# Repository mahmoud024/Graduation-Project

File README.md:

<h1 align="center">Graduation Project</h1>

## Our Idea

The goal of this project is to construct a physical FANET, outside the simulator, this can be done by constructing a number of drones built on the ESP-Drone repository, along with our own PCB and a 3D printed drone body. The FANET nodes will communicate with each other using LoRaWAN through our own modified AODV routing protocol. The FANET is planned to operate over the area of Birzeit University.

Since we will be using light-weight drones for nodes, the weight of anything carried by drones is critical, for this reason we decided on using the LoRa32 microcontroller, that integrates the ESP32 chip along with the LoRa module in a compact package, which weighs about 18grams, our testing shows a current draw of 45-50 mA during normal operations, goes up by 10 mA during transmission/reception

<div align="center">
  
</div>

## Step 1: Build ESP23 Drone

Since the scope of the project is rapidly expanding, we don’t have enough time
to design and build a drone from scratch, instead we will be using Espressif
Systems’ drone design.

For more information on getting started, visit the [Espressif ESP-Drone Documentation](https://docs.espressif.com/projects/espressif-esp-drone/en/latest/getespidf.html).

<h3 align="center">Hardware Part</h3>
   
1. **Components**

    We faced some difficulties in providing the parts because we are restricted by the Israeli occupation and the high cost of the parts, but the parts were eventually provided with great difficulty.

    - ##### Basic Component List
    <div align="center">
      
      | **Component**                         | **Number** | **Notes**                         |
      |---------------------------------------|------------|-----------------------------------|
      | Main board                            | 1          | ESP32 LORA V3 + MPU6050           |
      | Frame                                 | 1          | We Build it using 3D printer      |
      | 716 motor                             | 4          | Optional: 720 motor               |
      | 46mm propeller A                      | 2          |                                   |
      | 46mm propeller B                      | 2          |                                   |
      | 1000mAh 1s LiPo battery               | 1          |                                   |
      
    </div>

     1. **Frame**

      Steps to make the Frame:

      <div align="center">
          
      </div>

   Final Output:
   
    <div align="center">

    </div>

     2. **Main Controller**

      <div align="center">
          
      </div>

    <div align="center">

      | **Chip**       | **Module**           |     **Battery**       |    **Dimensions**     |
      |----------------|----------------------|-----------------------|-----------------------|
      | ESP32-S3FN8    | ESP32 LORA V3        | 3.7V lithium battery  |  50.2 * 25.5* 10.2 mm |

    </div>

     3. **Sensor**
        
      <div align="center">
          
      </div>
   
    <div align="center">
  
      | **Sensor**     | **Interface**        | **Notes**                             |
      |----------------|----------------------|---------------------------------------|
      | MPU6050        | I2C0                 | Main board sensor                     |
   
    </div>

    3. **Motor**
        
      <div align="center">
          
      </div>
   
    <div align="center">
  
      | **Motor**      | **Type**             | **Notes**                              |
      |----------------|----------------------|----------------------------------------|
      | 716 motor      | Coreless motor       | Use 720 if you have issue in altitude  |
   
    </div>

    3. **Battery**
        
      <div align="center">
          
      </div>
   
    <div align="center">
  
      | **Battery**             | **Voltage**     | **Dimensions**      | **Dimensions**    |
      |-------------------------|-----------------|---------------------|-------------------|
      | 1000mAh 1s LiPo battery | 3.7V (1S)       | 48 x 30 x 9         | 28.5              |
   
    </div>

    - ##### Definition of Main Board IO

    <div align="center">

      | **Pins**       | **Function**         | **Notes**                             |
      |----------------|----------------------|---------------------------------------|
      | GPIO23         | I2C0_SDA             | Only for MPU6050                      |
      | GPIO22         | I2C0_SCL             | Only for MPU6050                      |
      | GPIO2          | interrupt            | MPU6050 interrupt                     |
      | GPIO12         | MOT_1                |                                       |
      | GPIO35         | MOT_2                |                                       |
      | GPIO32         | MOT_3                |                                       |
      | GPIO33         | MOT_4                |                                       |
      | GND            |                      | With Ground                           |
      | 3V3            |                      | With VCC of MPU6050                   |

    </div>

2. **PCB**

    As is previously, our drone design is light-weight, so we will need to conserve as much as possible on the drone weight, and therefore we found it best to construct our own PCB.

    Scheme Below show our PCB design:

    <div align="center">
      
    </div>

    Steps to make our PCB:

    <div align="center">

    </div>

    The Link below show some videos While working on the production of the PCB (https://google.com)

    You Can Find All File You Needed in (PCB) Folder
---

<h3 align="center">Software Part</h3>

#### Set up ESP-IDF Environment

Please refer to [ ESP-IDF Programming Guide](https://docs.espressif.com/projects/esp-idf/en/release-v4.4/esp32s2/get-started/index.html) and set up ESP-IDF environmnet step by step.

* ESP-IDF branch release /v4.4 is suggested.

* Please follow and complete all setup steps.

* Build a example of ESP-IDF to make sure the setup is successful.

#### Get Project Source Code
###### Beta code, currently in the GitHub repository, is available by using git:

```
git clone https://github.com/espressif/esp-drone.git
```
###### The project software mainly consists of a flight control kernel, hardware drivers, and dependency libraries:

* The flight control kernel is from Crazyflie, mainly including hardware abstraction layer and flight control program.

* Hardware drivers are structured in files according to hardware interfaces, including I2C devcies and SPI devices.

* Dependency libraries include the default components provided by ESP-IDF, as well as DSP from third parties.

###### The code file structure is as follows:

#### Download and Install ESP-Drone APP

ESP-Drone APP is available for Android and iOS.

For Android, please scan the QR below to download ESP-Drone APP.

<div align="center">
  
</div>

For iOS, please search and download the ESP-Drone APP in App Store.

iOS APP source code: [ESP-Drone-iOS](https://github.com/EspressifApps/ESP-Drone-iOS)

Android APP source code: [ESP-Drone-Android](https://github.com/EspressifApps/ESP-Drone-Android)

#### Flight Control

* Click “Connect” button/icon at your APP. When the connection is established successfully between your drone and APP, the LED on the drone blinks GREEN.

* Slide “Thrust” slightly to take off the drone.

* Control the flight by moving your fingers on the APP.

<div align="center">
  
</div>

<div align="center">
  Android APP Interface
</div>

## Step 2: Routing Protocol

we will be using a LoRa module for transmission/Re- ception between nodes in our physical test bench, the LoRa module is chosen for its extended range, up to 14Km at SF12, and extremely low current draw, our own testing showed an 10 mA increase in current draw at transmission/re- ception at SF7, matching the datasheet specification.

The drawback to all this, is the low bandwidth, 290 bps at SF12, choosing a lower spread factor, will provide a higher bandwidth at a lower range, SF7 is rated to give 5470 bps for 2km, a range of 2km is well above our needs for this project, the bit rate is also sufficient for the communication protocol used, table 2 shows LoRa transmission ranges and bandwidth at different Spread Factors.

<div align="center">
  
  | **Spreading Factor** | **Bitrate** | **Range** |
  |----------------------|-------------|-----------|
  | SF7                  | 5470 bps    | 2 Km      |
  | SF8                  | 3125 bps    | 4 Km      |
  | SF9                  | 1760 bps    | 6 Km      |
  | SF10                 | 980 bps     | 8 Km      |
  | SF11                 | 440 bps     | 11 Km     |
  | SF12                 | 290 bps     | 14 Km     |

</div>

Our routing protocol builds upon the AODV protocol, and improves on it in two substantial ways, multiple paths and speed dependent route lifetime. The AODV routing protocol establishes a singular path for packets to travel from the source node to the destination node, however this can be unreliable in unstable networks, therefore establishing multiple paths will incur small overhead for the reward of a more reliable communication link, this is proposed in the AOMDV
routing protocol.

<div align="center">

| **Parameter**                    | **AODV**                    | **AOMDV**                    |
|----------------------------------|-----------------------------|------------------------------|
| Routing Protocol                 | Single path routing protocol | Multipath routing protocol   |
| Average End-to-End Delay         | 175 ms                      | 194 ms                       |
| Routing Overhead                 | Low                         | High                         |
| Number of Packets Dropped        | High                        | Low                          |
| Performance Metrics              | Low                         | High                         |

</div>

The AODV routing protocol doesn’t provide a method to calculate the lifetime of established routes between nodes, ns3 simulator keeps an arbitrary period of time of 10 seconds, we suggest making use of the instantaneous speed
of each node in the calculation of the lifetime, where the lifetime of any path is decided by the speed of the nodes in the path at route instantiation, equation below is followed when calculating the lifetime of any route established between any two nodes, where Sx is the speed of node x at the time of RREP packet transmission/forwarding, and  is scalar hyperparameter used for scaling the lifetime
of all routes.

<div align="center">

Life time Route = min(S<sub>0</sub>, S<sub>1</sub>, S<sub>2</sub>, &hellip;, S<sub>n</sub>) / &alpha;

</div>

Currently, we were able to construct the lifetime calculations on the ns3 simulator and it has yield promising results, as it outperformed the AODV protocol in terms on Packet Receive Rate, this is probably at the cost of increased routing calculations.

#### Multi-path implementation is currently stagnate as some unexpected difficulties were faced.
#

- <h4>Part 1: code inspection and review of ns3 aodv implementtion</h4>
- <h4>Part 2: code inspection of ns3 mobility models to obtain speed</h4>
- <h4>Part 3: implantation of speed reliant timeout</h4>
- <h4>Part 4: attempt at implementing multi-path protocol(fail)</h4>
- <h4>Part 5: implement RREQ and RERR counter</h4>
- <h4>Part 6: Simulation results at different max_distance parameter values</h4>

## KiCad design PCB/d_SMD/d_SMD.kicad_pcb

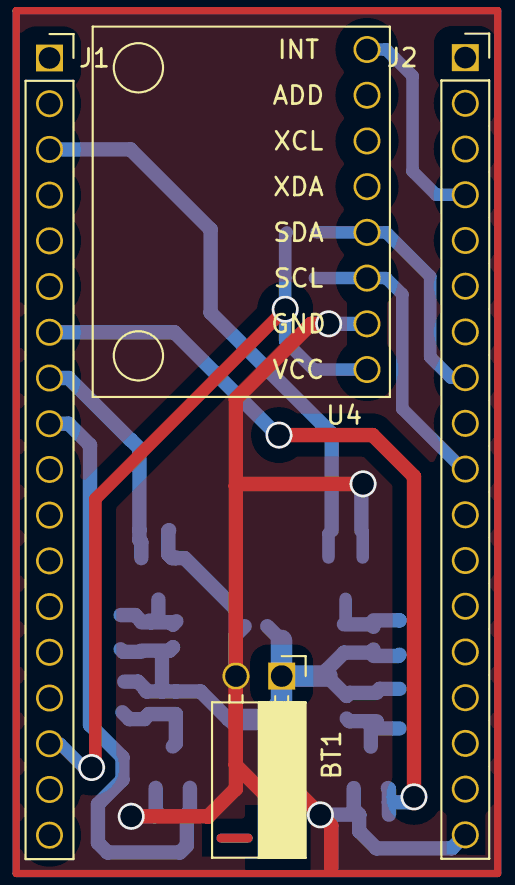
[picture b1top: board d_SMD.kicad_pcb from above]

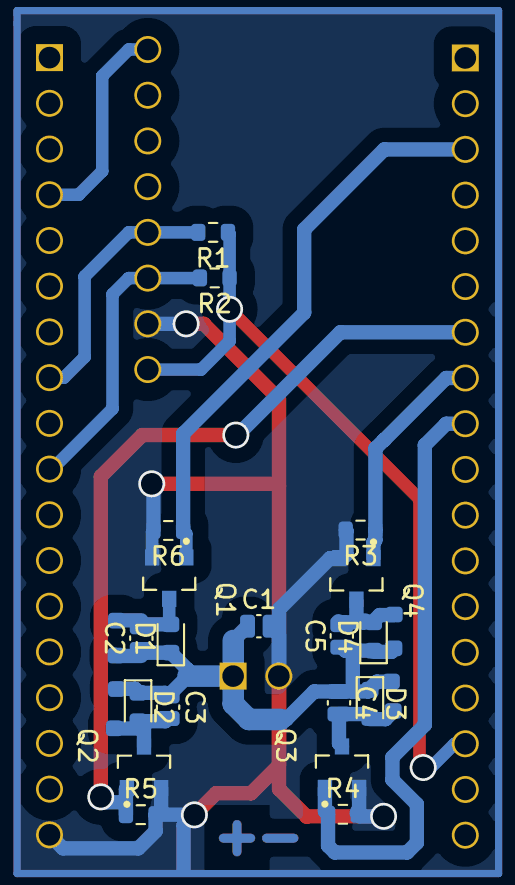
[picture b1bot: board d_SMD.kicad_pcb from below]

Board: 2 copper layers, 23 parts (19 on the bottom side), 14 nets.

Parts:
BT1: 3.7; PinSocket_1x02_P2.54mm_Horizontal
C1: 10uf; C_0504_1310Metric_Pad0.83x1.28mm_HandSolder
C2, C3, C4, C5: 1uf; C_0504_1310Metric_Pad0.83x1.28mm_HandSolder
D1, D2, D3, D4: D; D_0603_1608Metric
J1, J2: Conn_01x18_Socket; PinSocket_1x18_P2.54mm_Vertical
Q1, Q2, Q3, Q4: NMOS; TRANS_TSM250N02CX_RFG
R1, R2, R3, R4, R5, R6: 10k; R_0603_1608Metric
U4: module_mpu6050

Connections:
GND: BT1.2 (-), C1.2, J2.18, Q1.3 (S), Q2.3 (S), Q3.3 (S), Q4.3 (S), R3.2, R4.2, R5.2, R6.2, U4.2 (GND)
unnamed: BT1.1 (+), C1.1, C2.1, C3.1, C4.1, C5.1, D1.1 (K), D2.1 (K), D3.1 (K), D4.1 (K)
unnamed: C2.2, D1.2 (A), Q1.1 (D)
unnamed: C3.2, D2.2 (A), Q2.1 (D)
unnamed: C4.2, D3.2 (A), Q3.1 (D)
unnamed: C5.2, D4.2 (A), Q4.1 (D)
unnamed: J1.3, Q1.2 (G), R6.1
unnamed: J1.7, Q2.2 (G), R5.1
unnamed: J1.8, Q4.2 (G), R3.1
unnamed: J1.9, Q3.2 (G), R4.1
unnamed: J1.16, R1.1, R2.1, U4.1 (VCC)
unnamed: J2.4, U4.8 (INT)
unnamed: J2.8, R1.2, U4.4 (SDA)
unnamed: J2.10, R2.2, U4.3 (SCL)

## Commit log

2024-07-06 Create Project Report
2024-07-07 Added three folders and uploaded myFolder into folder1
